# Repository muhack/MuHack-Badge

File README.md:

# MuHack-Badge
Official repository for MuHack Badge.

The board features an RP2040 as main microcontroller running micropython.
Its job is to setup and stream data from the Bosh Sensor Hub BHI106(B), as well as controlling the LEDs.

```Hardware/``` folder contains the KiCad project

```Software/``` folder contains the BOSS system and the sketches for the ESP32 (WIP)

> **NOTE: The software is still in development, so expect A LOT OF bugs and missing features.**

## Chagelog v2

 - Added USB connector for the ESP32
 - Added NFC subsystem
 - Completely reworked the power system
 - Added more LEDs for battery status and esp32
 - Added a button for the ESP32
 - WIP: firmware update for better BHI support

## Chagelog v1
 - Initial release

## TODOs:
 - [x] Connect the interrupt line of BHI to the RP2040
 - [x] Invert TX/RX of UART between ESP32 and RP2040
 - [x] Change to a bigger footprint of ESP32 debug port
 - [x] Maybe add two button for boot sel and reset for the ESP32
 - [x] ~~Change~~ Remove battery switch
 - [x] Improve silkscreen text size
 - [x] Add silkscreen label for many things (pinout, battery polarity, etc)
 - [x] Expose BHI's internal I2C and interrupt line (for future sensors)
 - [x] Move I2C pull-up resistor
 - [x] Add leds and diods polarity
 - [x] Remove power inductor (or change to an available one)
 - [ ] ~~Maybe add a way to switch LEDs data line to the ESP32 instead of the RP2040~~
 - [ ] Docs and code comments
 - [x] Remove the D16 Schottky Diode from the battery line
 - [x] Maybe add some more cap to prevent brown-out when disconnecting USB power
 - [ ] Add a method within BHY library to stop every sensor
 - [x] Add NFC subsystem
 - [x] Add USB connector for the ESP32
  
 Special Thanks to:
 @gcammisa and Paolino

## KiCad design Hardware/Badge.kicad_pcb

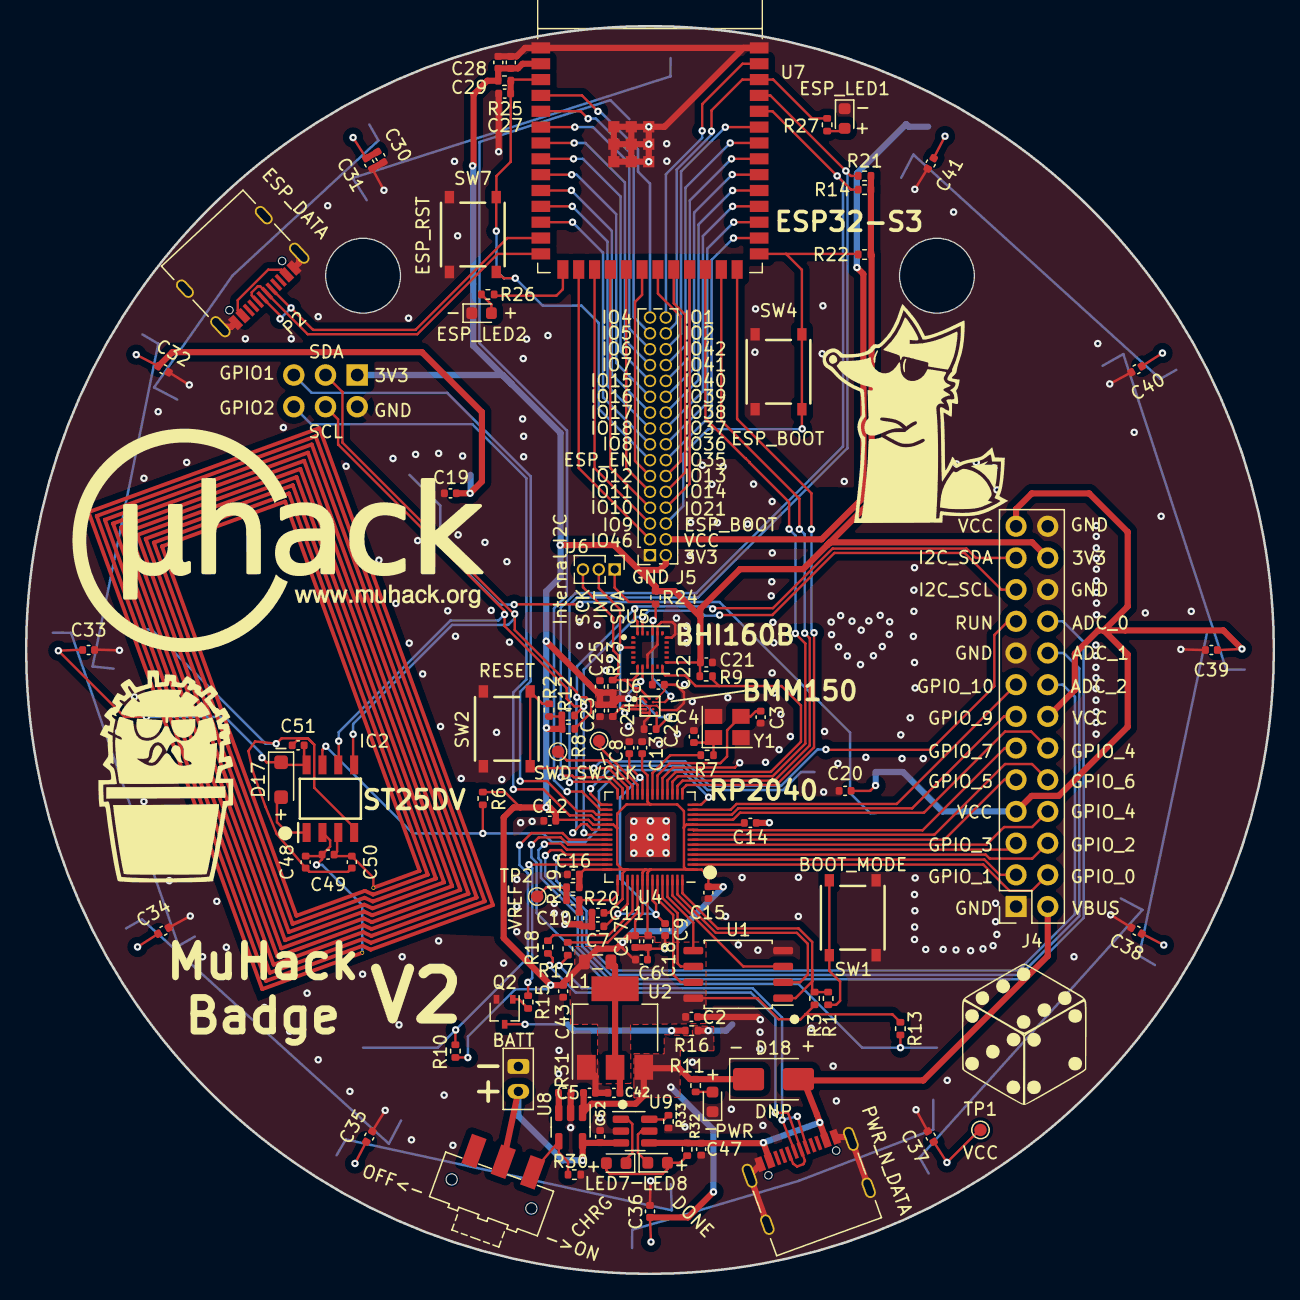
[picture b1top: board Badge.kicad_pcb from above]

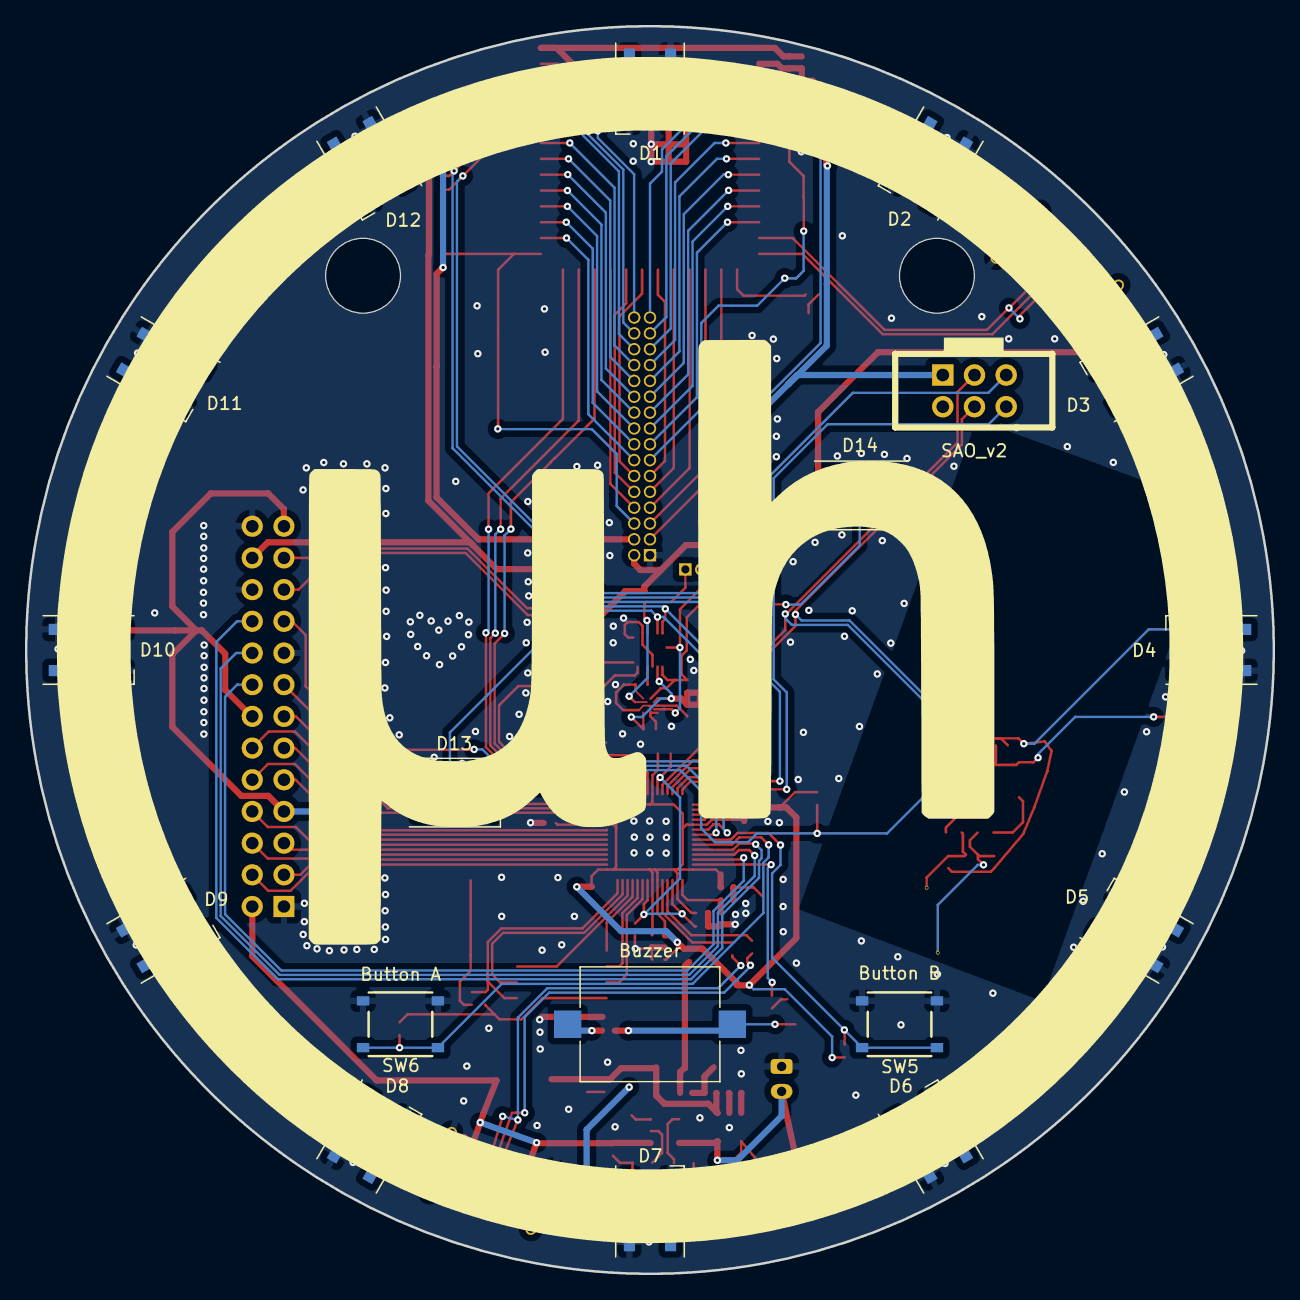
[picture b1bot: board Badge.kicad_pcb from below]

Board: 2 copper layers, 100.0 x 100.0 mm, 130 parts (18 on the bottom side), 119 nets.

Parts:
A1: MuTag_NFC_Antenna; muhack_badge_antenna
BT1: BATT; JST_PH_B2B-PH-K_1x02_P2.00mm_Vertical
BZ1: Buzzer; Buzzer_Mallory_AST1109MLTRQ
C2, C5, C6, C7, C8, C12, C13, C14, C15, C16, C17, C18, C21, C24, C25, C26, C29, C42: 100n; C_0402_1005Metric
C3, C4: 27p; C_0402_1005Metric
C9, C10, C11, C23, C27: 1u; C_0402_1005Metric
C19, C20, C28, C30, C31, C32, C33, C34, C35, C36, C37, C38, C39, C40, C41: 10u; C_0402_1005Metric
C22: 470n; C_0402_1005Metric
C43: 10n; C_0402_1005Metric
C47, C52: 4.7uF; C_0402_1005Metric
C48, C49, C50: DNP; C_0402_1005Metric
C51: 10nF; C_0402_1005Metric
D1, D2, D3, D4, D5, D6, D7, D8, D9, D10, D11, D12, D13, D14: WS2812B; LED_WS2812B_PLCC4_5.0x5.0mm_P3.2mm
D17: D; D_SOD-123F
D18: DNP; D_SMA
IC2: ST25DV; SOIC127P600X175-8N
J4: Conn_02x15_Counter_Clockwise; PinSocket_2x13_P2.54mm_Vertical
J5: Conn_01x12; PinSocket_2x16_P1.27mm_Vertical
J6: Internal_I2C; PinHeader_1x03_P1.27mm_Vertical
L1: 2.2uH; L_0805_2012Metric
LED2: ESP_LED2; LED_0603_1608Metric
LED3: PWR; LED_0603_1608Metric
LED4: ESP_LED1; LED_0603_1608Metric
LED7: CHRG; LED_0603_1608Metric
LED8: DONE; LED_0603_1608Metric
P1: PWR_N_DATA; USB_C_Receptacle_Palconn_UTC16-G
P2: ESP_DATA; USB_C_Receptacle_Palconn_UTC16-G
Q2: 2SC4213; SOT-323_SC-70
R1, R7, R32: 1k; R_0402_1005Metric
R2, R10, R13, R14, R21, R22, R25: 10k; R_0402_1005Metric
R3: DNF 10k; R_0402_1005Metric
R6, R8, R9, R12, R23, R24, R31: 4.7k; R_0402_1005Metric
R11, R26, R27: 470; R_0402_1005Metric
R15, R16, R33: 2k; R_0402_1005Metric
R17, R18, R19, R20: 27.4; R_0402_1005Metric
R30: 100k; R_0402_1005Metric
SW1: BOOT_MODE; TS-1187A-B-A-B
SW2: RESET; TS-1187A-B-A-B
SW4: ESP_BOOT; TS-1187A-B-A-B
SW5: Button B; TS-1187A-B-A-B
SW6: Button A; TS-1187A-B-A-B
SW7: ESP_RST; TS-1187A-B-A-B
SW9: PWR_SWT; SW_SPDT_CK-JS102011SAQN
TP1: VCC; TestPoint_Pad_D1.0mm
TP2: VREF; TestPoint_Pad_D1.0mm
TP3: SWCLK; TestPoint_Pad_D1.0mm
TP4: SWD; TestPoint_Pad_D1.0mm
U1: W25Q128JVS; SOIC-8_5.23x5.23mm_P1.27mm
U2: AMS1117-3.3; SOT-223-3_TabPin2
U4: RP2040; QFN-56-1EP_7x7mm_P0.4mm_EP3.2x3.2mm
U5: BHI160B; Bosch_Sensortec-BHI160B-MFG
U6: BMM150; Bosch_Sensortec-BMM150-IPC_B
U7: ESP32-S3; ESP32-S3-WROOM-1
U8: SY6280AAC; SOT-23-5
U9: TP4057; SOT-23-6
X1: SAO_v2; Simple_Addon_v2-BADGE-2x3
Y1: 12MHz_GND24; Crystal_SMD_3225-4Pin_3.2x2.5mm

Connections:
+1V1: C7.1, C8.1, C9.2, U4.23 (DVDD), U4.45 (VREG_VOUT), U4.50 (DVDD)
+3V3: C2.1, C6.2, C11.1, C12.2, C13.2, C14.2, C15.2, C16.2, C17.2, C18.2, C21.2, C23.1, C24.1, C25.2, C26.2, C28.1, C29.1, C43.2, J4.24, J5.2, L1.1, R2.2, R3.1, R6.1, R8.1, R9.1, R10.1, R12.1, R13.1, R14.2, R19.2, R21.2, R22.1, R23.1, R24.1, R25.1, U1.8 (VCC), U4.1 (IOVDD), U4.10 (IOVDD), U4.22 (IOVDD), U4.33 (IOVDD), U4.42 (IOVDD), U4.44 (VREG_IN), U4.48 (USB_VDD), U4.49 (IOVDD), U5.8 (VDDIO), U5.13 (VDD), U6.A1 (PS), U6.B2 (VDDIO), U6.E5 (VDD), U7.2 (3V3), X1.1 (3v3)
/ADC_0: J4.20, U4.38 (GPIO26_ADC0)
/ADC_1: J4.18, U4.39 (GPIO27_ADC1)
/ADC_2: J4.16, U4.40 (GPIO28_ADC2)
/ADC_AVDD: C10.1, R20.1, U4.43 (ADC_AVDD)
/ADC_BUZZ: R15.1, U4.41 (GPIO29_ADC3)
/ADC_VREF: R19.1, R20.2, TP2.1
/ESP_45: U4.15 (GPIO12), U7.26 (GPIO45)
/ESP_47: U4.17 (GPIO14), U7.24 (GPIO47/SPICLK_P/SUBSPICLK_P_DIFF)
/ESP_48: U4.16 (GPIO13), U7.25 (GPIO48/SPICLK_N/SUBSPICLK_N_DIFF)
/ESP_BOOT: J5.6, R22.2, SW4.2, U7.27 (GPIO0/BOOT)
/ESP_EN: C27.2, J5.13, R25.2, SW7.2, U7.3 (EN)
/ESP_RX: R14.1, U4.27 (GPIO16), U7.36 (U0RXD/GPIO44/CLK_OUT2)
/ESP_TX: R21.1, U4.28 (GPIO17), U7.37 (U0TXD/GPIO43/CLK_OUT1)
/GPIO_0: J4.4, U4.2 (GPIO0)
/GPIO_1: J4.3, U4.3 (GPIO1)
/GPIO_2: J4.6, U4.4 (GPIO2)
/GPIO_3: J4.5, U4.5 (GPIO3)
/GPIO_4: J4.8, U4.6 (GPIO4)
/GPIO_5: J4.9, U4.7 (GPIO5)
/GPIO_6: J4.10, U4.8 (GPIO6)
/GPIO_7: J4.11, U4.9 (GPIO7)
/GPIO_8: J4.12, U4.11 (GPIO8)
/GPIO_9: J4.13, U4.12 (GPIO9)
/GPIO_10: J4.15, U4.13 (GPIO10)
/Gyros/INT_S1: J6.2, U5.3 (GPIO1), U6.D2 (INT)
/Gyros/INT_SCK: J6.3, R23.2, U5.7 (ASCK), U6.A3 (SCK)
/Gyros/INT_SDA: J6.1, R24.2, U5.21 (ASDA), U6.B4 (SDI)
/I2C_SCL: IC2.6 (SCL), J4.21, R12.2, U4.35 (GPIO23), U5.23 (SCK), X1.4 (SCL)
/I2C_SDA: IC2.5 (SDA), J4.23, R8.2, U4.34 (GPIO22), U5.24 (SDA), X1.3 (SDA)
/LED_POST: D13.4 (DIN), U4.29 (GPIO18)
/LED_STRIPE: D1.4 (DIN), U4.30 (GPIO19)
/NFC/NFC_V_EH: D17.2 (A), IC2.1 (V_EH)
/NFC_INT: IC2.7 (GPO(OD)), R6.2, U4.14 (GPIO11)
/QSPI_SCLK: U1.6 (CLK), U4.52 (QSPI_SCLK)
/QSPI_SD0: U1.5 (DI(IO0)), U4.53 (QSPI_SD0)
/QSPI_SD1: U1.2 (DO(IO1)), U4.55 (QSPI_SD1)
/QSPI_SD2: U1.3 (IO2), U4.54 (QSPI_SD2)
/QSPI_SD3: U1.7 (IO3), U4.51 (QSPI_SD3)
/QSPI_SS: R1.2, R3.2, U1.1 (~CS), U4.56 (QSPI_SS)
/RUN: J4.19, R2.1, SW2.1, U4.26 (RUN)
/SAO_1: U4.31 (GPIO20), X1.5 (GPIO1)
/SAO_2: U4.32 (GPIO21), X1.6 (GPIO2)
/SEN_INT: R9.2, U4.18 (GPIO15), U5.12 (INT)
/SWCLK: TP3.1, U4.24 (SWCLK)
/SWD: TP4.1, U4.25 (SWD)
/SW_1: R10.2, SW5.2, U4.36 (GPIO24)
/SW_2: R13.2, SW6.2, U4.37 (GPIO25)
/USB_D+: P1.A6 (D+), P1.B6 (D+), R17.1
/USB_D-: P1.A7 (D-), P1.B7 (D-), R18.2
/WiFi_BT/ESP_USB+: P2.A6 (D+), P2.B6 (D+), U7.14 (GPIO20/U1CTS/ADC2_CH9/CLK_OUT1/USB_D+)
/WiFi_BT/ESP_USB-: P2.A7 (D-), P2.B7 (D-), U7.13 (GPIO19/U1RTS/ADC2_CH8/CLK_OUT2/USB_D-)
/WiFi_BT/IO1: J5.32, U7.39 (GPIO1/TOUCH1/ADC1_CH0)
/WiFi_BT/IO2: J5.30, R27.1, U7.38 (GPIO2/TOUCH2/ADC1_CH1)
/WiFi_BT/IO3: R26.1, U7.15 (GPIO3/TOUCH3/ADC1_CH2)
/WiFi_BT/IO4: J5.31, U7.4 (GPIO4/TOUCH4/ADC1_CH3)
/WiFi_BT/IO5: J5.29, U7.5 (GPIO5/TOUCH5/ADC1_CH4)
/WiFi_BT/IO6: J5.27, U7.6 (GPIO6/TOUCH6/ADC1_CH5)
/WiFi_BT/IO7: J5.25, U7.7 (GPIO7/TOUCH7/ADC1_CH6)
/WiFi_BT/IO8: J5.15, U7.12 (GPIO8/TOUCH8/ADC1_CH7/SUBSPICS1)
/WiFi_BT/IO9: J5.5, U7.17 (GPIO9/TOUCH9/ADC1_CH8/FSPIHD/SUBSPIHD)
/WiFi_BT/IO10: J5.7, U7.18 (GPIO10/TOUCH10/ADC1_CH9/FSPICS0/FSPIIO4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)
/WiFi_BT/IO11: J5.9, U7.19 (GPIO11/TOUCH11/ADC2_CH0/FSPID/FSPIIO5/S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)
/WiFi_BT/IO12: J5.11, U7.20 (GPIO12/TOUCH12/ADC2_CH1/FSPICLK/FSPIIO6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)
/WiFi_BT/IO13: J5.12, U7.21 (GPIO13/TOUCH13/ADC2_CH2/FSPIQ/FSPIIO7/S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)
/WiFi_BT/IO14: J5.10, U7.22 (GPIO14/TOUCH14/ADC2_CH3/FSPIWP/FSPIDQS/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)
/WiFi_BT/IO15: J5.23, U7.8 (GPIO15/U0RTS/ADC2_CH4/XTAL_32K_P)
/WiFi_BT/IO16: J5.21, U7.9 (GPIO16/U0CTS/ADC2_CH5/XTAL_32K_NH5)
/WiFi_BT/IO17: J5.19, U7.10 (GPIO17/U1TXD/ADC2_CH6)
/WiFi_BT/IO18: J5.17, U7.11 (GPIO18/U1RXD/ADC2_CH7/CLK_OUT3)
/WiFi_BT/IO21: J5.8, U7.23 (GPIO21)
/WiFi_BT/IO35: J5.14, U7.28 (SPIIO6/GPIO35/FSPID/SUBSPID)
/WiFi_BT/IO36: J5.16, U7.29 (SPIIO7/GPIO36/FSPICLK/SUBSPICLK)
/WiFi_BT/IO37: J5.18, U7.30 (SPIDQS/GPIO37/FSPIQ/SUBSPIQ)
/WiFi_BT/IO38: J5.20, U7.31 (GPIO38/FSPIWP/SUBSPIWP)
/WiFi_BT/IO39: J5.22, U7.32 (MTCK/GPIO39/CLK_OUT3/SUBSPICS1)
/WiFi_BT/IO40: J5.24, U7.33 (MTDO/GPIO40/CLK_OUT2)
/WiFi_BT/IO41: J5.26, U7.34 (MTDI/GPIO41/CLK_OUT1)
/WiFi_BT/IO42: J5.28, U7.35 (MTMS/GPIO42)
/WiFi_BT/IO46: J5.3, U7.16 (GPIO46)
/XIN: C3.2, U4.20 (XIN), Y1.3
/XOUT: R7.2, U4.21 (XOUT)
/~USB_BOOT: R1.1, SW1.2
GND: BT1.2 (-), C2.2, C3.1, C4.1, C5.1, C6.1, C7.2, C8.2, C9.1, C10.2, C11.2, C12.1, C13.1, C14.1, C15.1, C16.1, C17.1, C18.1, C19.2, C20.2, C21.1, C22.2, C23.2, C24.2, C25.1, C26.1, C27.1, C28.2, C29.2, C30.2, C31.2, C32.2, C33.2, C34.2, C35.2, C36.2, C37.2, C38.2, C39.2, C40.2, C41.2, C42.1, C43.1, C47.2, C48.1, C50.2, C51.2, C52.2, D1.3 (VSS), D2.3 (VSS), D3.3 (VSS), D4.3 (VSS), D5.3 (VSS), D6.3 (VSS), D7.3 (VSS), D8.3 (VSS), D9.3 (VSS), D10.3 (VSS), D11.3 (VSS), D12.3 (VSS), D13.3 (VSS), D14.3 (VSS), IC2.4 (VSS), J4.1, J4.17, J4.22, J4.26, J5.1, LED2.1 (K), LED3.1 (K), LED4.1 (K), P1.A1 (GND), P1.A12 (GND), P1.B1 (GND), P1.B12 (GND), P1.S1 (SHIELD), P2.A1 (GND), P2.A12 (GND), P2.B1 (GND), P2.B12 (GND), P2.S1 (SHIELD), Q2.2 (E), R30.1, R31.1, R33.1, SW1.1, SW2.2, SW4.1, SW5.1, SW6.1, SW7.1, U1.4 (GND), U2.1 (GND), U4.19 (TESTEN), U4.57 (GND), U5.9 (SA_GPIO7), U5.18 (GND), U5.20 (GNDIO), U6.A5 (CSB), U6.C1 (SDO), U6.C5 (GND), U6.E1 (GND), U6.E3 (GND), U7.1 (GND), U7.40 (GND), U7.41 (GND), U8.2 (GND), U9.2 (GND), X1.2 (GND), Y1.2, Y1.4
unnamed: A1.1 (IN), C48.2, C49.1, IC2.2 (AC0)
unnamed: A1.2 (OUT), C49.2, C50.1, IC2.3 (AC1)
unnamed: BT1.1 (+), C52.1, SW9.2 (B), U8.5 (IN), U9.3 (BAT)
unnamed: BZ1.2 (+), Q2.3 (C), R16.2
unnamed: C4.2, R7.1, Y1.1
unnamed: D1.2 (DOUT), D2.4 (DIN)
unnamed: D2.2 (DOUT), D3.4 (DIN)
unnamed: D3.2 (DOUT), D4.4 (DIN)
unnamed: D4.2 (DOUT), D5.4 (DIN)
unnamed: D5.2 (DOUT), D6.4 (DIN)
unnamed: D6.2 (DOUT), D7.4 (DIN)
unnamed: D7.2 (DOUT), D8.4 (DIN)
unnamed: D8.2 (DOUT), D9.4 (DIN)
unnamed: D9.2 (DOUT), D10.4 (DIN)
unnamed: D10.2 (DOUT), D11.4 (DIN)
unnamed: D11.2 (DOUT), D12.4 (DIN)
unnamed: D13.2 (DOUT), D14.4 (DIN)
unnamed: LED2.2 (A), R26.2
unnamed: LED3.2 (A), R11.2
unnamed: LED4.2 (A), R27.2
unnamed: LED7.2 (A), LED8.2 (A), R32.1
unnamed: LED7.1 (K), U9.1 (~CHRG)
unnamed: LED8.1 (K), U9.5 (~STDBY)
unnamed: P2.A4 (VBUS), P2.A9 (VBUS), P2.B4 (VBUS), P2.B9 (VBUS)
unnamed: Q2.1 (B), R15.2
unnamed: R30.2, SW9.1 (A), U8.4 (ON)
unnamed: C42.2, L1.2, U2.2 (VO)
unnamed: R18.1, U4.46 (USB_DM)
unnamed: R17.2, U4.47 (USB_DP)
unnamed: C22.1, U5.10 (VREG)
unnamed: R31.2, U8.3 (SET)
unnamed: R33.2, U9.6 (PROG)
VBUS: C47.1, D18.2 (A), J4.2, P1.A4 (VBUS), P1.A9 (VBUS), P1.B4 (VBUS), P1.B9 (VBUS), R32.2, U9.4 (VCC)
VCC: BZ1.1 (-), C5.2, C19.1, C20.1, C30.1, C31.1, C32.1, C33.1, C34.1, C35.1, C36.1, C37.1, C38.1, C39.1, C40.1, C41.1, C51.1, D1.1 (VDD), D2.1 (VDD), D3.1 (VDD), D4.1 (VDD), D5.1 (VDD), D6.1 (VDD), D7.1 (VDD), D8.1 (VDD), D9.1 (VDD), D10.1 (VDD), D11.1 (VDD), D12.1 (VDD), D13.1 (VDD), D14.1 (VDD), D17.1 (K), D18.1 (K), IC2.8 (VCC), J4.7, J4.14, J4.25, J5.4, R11.1, R16.1, TP1.1, U2.3 (VI), U8.1 (OUT)

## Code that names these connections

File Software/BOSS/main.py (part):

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NFC_I2C_ADDR = 0x53 # 83dec for access to user memory, Dynamic registers or Mailbox, 0x57 (87dec) for system area

## Interrupts PINs ##
NFC_INT_PIN = 11
BHI_INT_PIN = 15

## ESP32 communication PINs ##
ESP_TX_PIN = 16
ESP_RX_PIN = 17
ESP_COM_PIN_45 = 12
ESP_COM_PIN_48 = 13
ESP_COM_PIN_47 = 14
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LED_LETTER_PIN = 18
LED_LETTER_LEN = 2

LED_STRIPE_PIN = 19
LED_STRIPE_LEN = 12

## Buzzer and Buttons PINs ##
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button_B = machine.Pin(BUTTON_B_PIN, Pin.IN)

bhy = BHY(MAIN_I2C, address=BHY_I2C_ADDR, int_pin=BHI_INT_PIN, debug=False)
nfc = NFC(MAIN_I2C, address=NFC_I2C_ADDR, int_pin=NFC_INT_PIN, debug=False)
cled = CLED(LED_STRIPE_PIN, LED_STRIPE_LEN, LED_LETTER_PIN, LED_LETTER_LEN, debug=False)

## Startup chime ##
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remapping_matrix = [1,0,0,0,1,0,0,0,-1] # P? ? - obtained from experimenting with the accelerometer

def testHardware():
    led_stripe = neopixel.NeoPixel(machine.Pin(LED_STRIPE_PIN), LED_STRIPE_LEN)
    led_letter = neopixel.NeoPixel(machine.Pin(LED_LETTER_PIN), LED_LETTER_LEN)
    try:
        print("Testing LED Stripe")
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    except ImportError:
        import asyncio

    tl = trickLED.TrickLED(machine.Pin(LED_STRIPE_PIN), LED_STRIPE_LEN)
    tl_letters = trickLED.TrickLED(machine.Pin(LED_LETTER_PIN), LED_LETTER_LEN)

    async def play(animation, n_frames, **kwargs):
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
    COMMAND_SENSOR = "SENSOR"
    COMMAND_CLED = "CLED"
    esp_uart = machine.UART(0, 115200, tx=Pin(ESP_TX_PIN), rx=Pin(ESP_RX_PIN))
    esp_uart.init(115200, bits=8, parity=None, stop=1, tx=Pin(ESP_TX_PIN), rx=Pin(ESP_RX_PIN))
        
    # For good measure, flush old data
    bhy.flushFifo() # TODO: THIS DONT WORKS AS EXPECTED
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
    # Then we install the wakeup interrupt
    # Pin.irq(handler=None, trigger=Pin.IRQ_FALLING | Pin.IRQ_RISING, *, priority=1, wake=None, hard=False)
    #machine.Pin(NFC_INT_PIN).irq(trigger=Pin.IRQ_RISING, handler=wakeup, wake=machine.DEEPSLEEP)
    #nfc_gpo = machine.Pin(NFC_INT_PIN, machine.Pin.IN)

    if auto_start is not None: # The user configured an app to be automatically started
        try:
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
def UARTPassThrough():
    try:
        esp_uart = machine.UART(0, 115200, tx=Pin(ESP_TX_PIN), rx=Pin(ESP_RX_PIN))

        sys_uart_thread = _thread.start_new_thread(from_stdin_to_uart, (esp_uart,1))
        while True:
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    # btn6.irq(lambda e: print("button 6 event!"), Pin.IRQ_RISING | Pin.IRQ_FALLING) 
    # lowpower.dormant_until_pin(BUTTON_A_PIN)
    # # lowpower.dormant_with_modes({
    # #     NFC_INT_PIN: (lowpower.EDGE_LOW | lowpower.EDGE_HIGH),
    # # })
    # print("after dormant") # only print after receiving signal on Pin number DORMANT_PIN

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
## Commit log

2022-10-26 First Commit - version 1.0
2022-10-27 Added SAOv2 Connector - re-arranged some RP pins connection
2022-10-27 Connected both USB-C data signal, moved the crystal - revisisted ready for production
2022-11-24 First BOSS commit, added BasicOTA (not working), updated Hardware .gitignore
2022-11-24 Update READMEs
2022-11-25 Change License
2022-11-25 Improved the headless mode, CLED system and minor bug fix - UNSATBLE
2022-11-25 Headless mode is working, added idle animation - there are still some bugs with CLED
2022-11-29 Added drawVector and Linear Acceleration app
2022-11-29 Updated TODOs and re-enabled startup sound
2023-04-03 Inverted TX/RX from ESP32 - added INT line from BHI - Changed ESP32 dbg port to bigger footprint
2023-06-22 First modification for v2
2023-06-28 WIP - Added NFC Antenna and connected almost everythings else
2023-06-29 All upgrade done, start working on lesser stuff (like silkscreen)
2023-06-30 TODO list completed - need to search for components
2023-07-06 Testing with different power circuit
2023-07-06 Ready to order - THE POWER DIODE IS MISSING (need futher investigations)
2023-07-10 Reworked the power system - ORDERED ON JLCPCB
2023-07-20 First draft of the NFC subsystem - reading and writing are working
2023-08-02 Added trickLED animation - fixed some bug - SENSORS DONT WORK
2023-08-04 Resolved the BHI160 problem: all sensors and headless mode working - First draft for NFC wakeup from deepsleep (NOT WORKING)
2023-08-10 Working ball program - but the headless version crashes when it is launched
2023-08-11 Bug fix for headless ball program - added header license to files - add license for trickLED - cleared boot and autostart procedure
2023-08-11 Re-added WebServer.cpp (WIP)
2023-08-11 Update the READMEs

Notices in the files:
Software/BOSS/main.py:
Copyright (C) 2021 MrMoDDoM
modify it under the terms of the GNU Affero General Public License v3.0
